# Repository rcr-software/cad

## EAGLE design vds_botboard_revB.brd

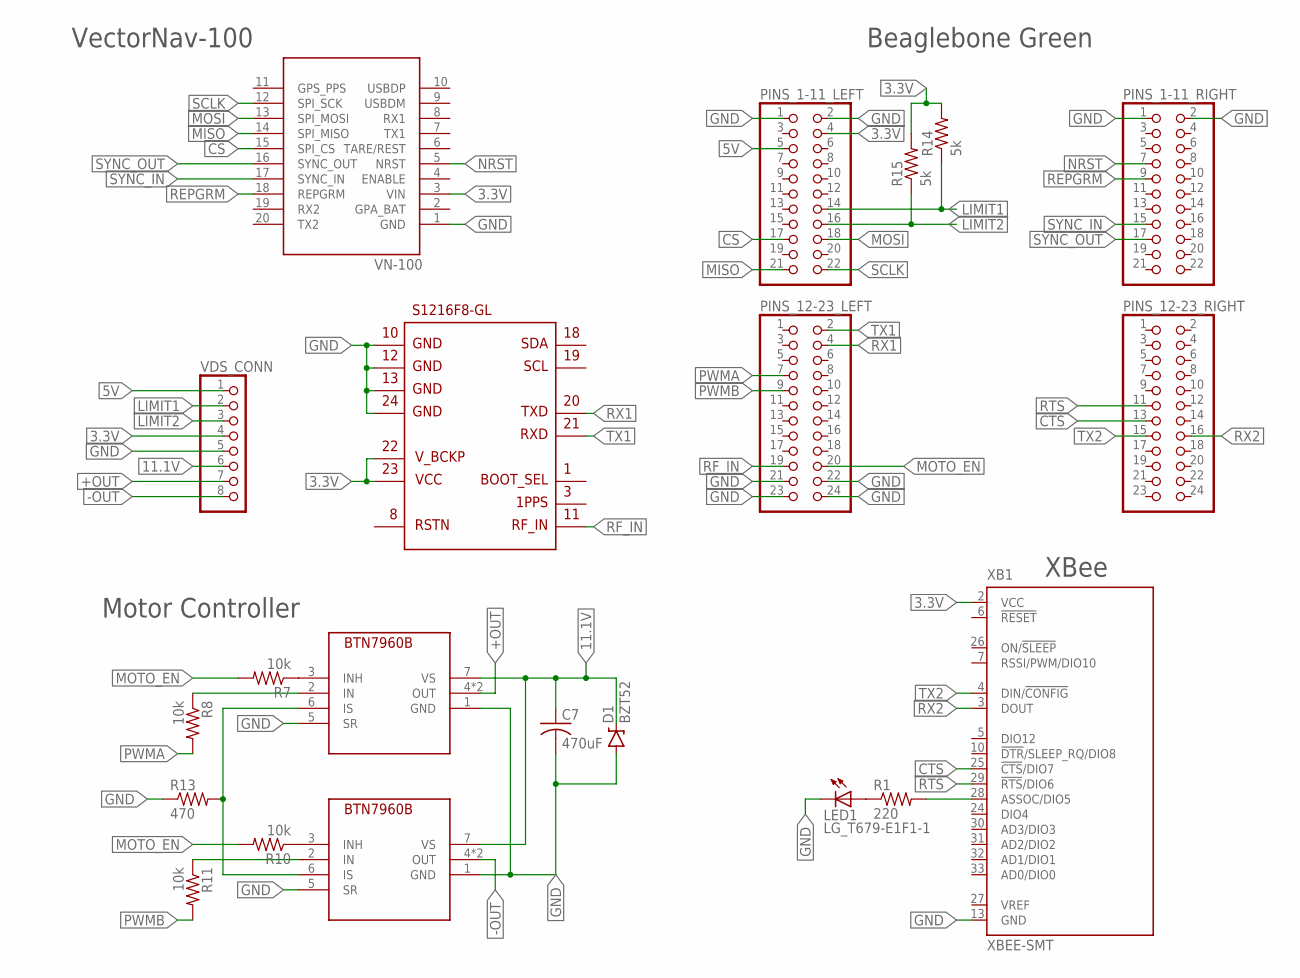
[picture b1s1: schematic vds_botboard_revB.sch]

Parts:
C7: 470uF; C050-024X044
D1: BZT52; DIODE-BZT52
JM1: S1216F8-GL
LED1: LG_T679-E1F1-1; PLCC2
PINS_1-11_LEFT, PINS_1-11_RIGHT: PINHD-2X11; 2X11
PINS_12-23_LEFT, PINS_12-23_RIGHT: PINHD-2X12; 2X12
R1: 220; 0204/5
R7, R8, R10, R11: 10k; 0204/5
R13: 470; 0204/5
R14, R15: 5k; 0204/5
U1, U2: INF-PG-TO263-7-1_L_1_BTN7960B; INF-PG-TO263-7-1_L_1PRIMARY
VDS_CONN: PINHD-1X8; 1X08
VN1: VECTORNAV-100; VN-100
XB1: XBEE-SMT

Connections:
3.3V: JM1.22, JM1.23, PINS_1-11_LEFT.4, R14.2, R15.2, VDS_CONN.4, VN1.3 (VIN), XB1.2 (VCC)
5V: PINS_1-11_LEFT.5, VDS_CONN.1
11.1V: C7.1, D1.C, U1.7 (VS), U2.7 (VS), VDS_CONN.6
+OUT: U1.4 (OUT), U1.8 (OUT), VDS_CONN.7
-OUT: U2.4 (OUT), U2.8 (OUT), VDS_CONN.8
COMM: R1.2, XB1.28 (ASSOC/DIO5)
CS: PINS_1-11_LEFT.17, VN1.15 (SPI_CS)
CTS: PINS_12-23_RIGHT.13, XB1.25 (!CTS!/DIO7)
GND: C7.2, D1.A, JM1.10, JM1.12, JM1.13, JM1.24, LED1.C, PINS_1-11_LEFT.1, PINS_1-11_LEFT.2, PINS_1-11_RIGHT.1, PINS_1-11_RIGHT.2, PINS_12-23_LEFT.21, PINS_12-23_LEFT.22, PINS_12-23_LEFT.23, PINS_12-23_LEFT.24, R13.1, U1.1 (GND), U1.5 (SR), U2.1 (GND), U2.5 (SR), VDS_CONN.5, VN1.1 (GND), XB1.13 (GND)
IS: R13.2, U1.6 (IS), U2.6 (IS)
LIMIT1: PINS_1-11_LEFT.14, R14.1, VDS_CONN.2
LIMIT2: PINS_1-11_LEFT.16, R15.1, VDS_CONN.3
MISO: PINS_1-11_LEFT.21, VN1.14 (SPI_MISO)
MOSI: PINS_1-11_LEFT.18, VN1.13 (SPI_MOSI)
MOTO_EN: PINS_12-23_LEFT.20, R7.2, R10.2
unnamed: LED1.A, R1.1
unnamed: R7.1, U1.3 (INH)
unnamed: R8.1, U1.2 (IN)
unnamed: R10.1, U2.3 (INH)
unnamed: R11.1, U2.2 (IN)
NRST: PINS_1-11_RIGHT.7, VN1.5 (NRST)
PWMA: PINS_12-23_LEFT.7, R8.2
PWMB: PINS_12-23_LEFT.9, R11.2
REPGRM: PINS_1-11_RIGHT.9, VN1.18 (REPGRM)
RF_IN: JM1.11, PINS_12-23_LEFT.19
RTS: PINS_12-23_RIGHT.11, XB1.29 (!RTS!/DIO6)
RX1: JM1.20, PINS_12-23_LEFT.4
RX2: PINS_12-23_RIGHT.16, XB1.3 (DOUT)
SCLK: PINS_1-11_LEFT.22, VN1.12 (SPI_SCK)
SYNC_IN: PINS_1-11_RIGHT.15, VN1.17 (SYNC_IN)
SYNC_OUT: PINS_1-11_RIGHT.17, VN1.16 (SYNC_OUT)
TX1: JM1.21, PINS_12-23_LEFT.2
TX2: PINS_12-23_RIGHT.15, XB1.4 (DIN/!CONFIG)

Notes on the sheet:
VectorNav-100
Motor Controller
Beaglebone Green
XBee

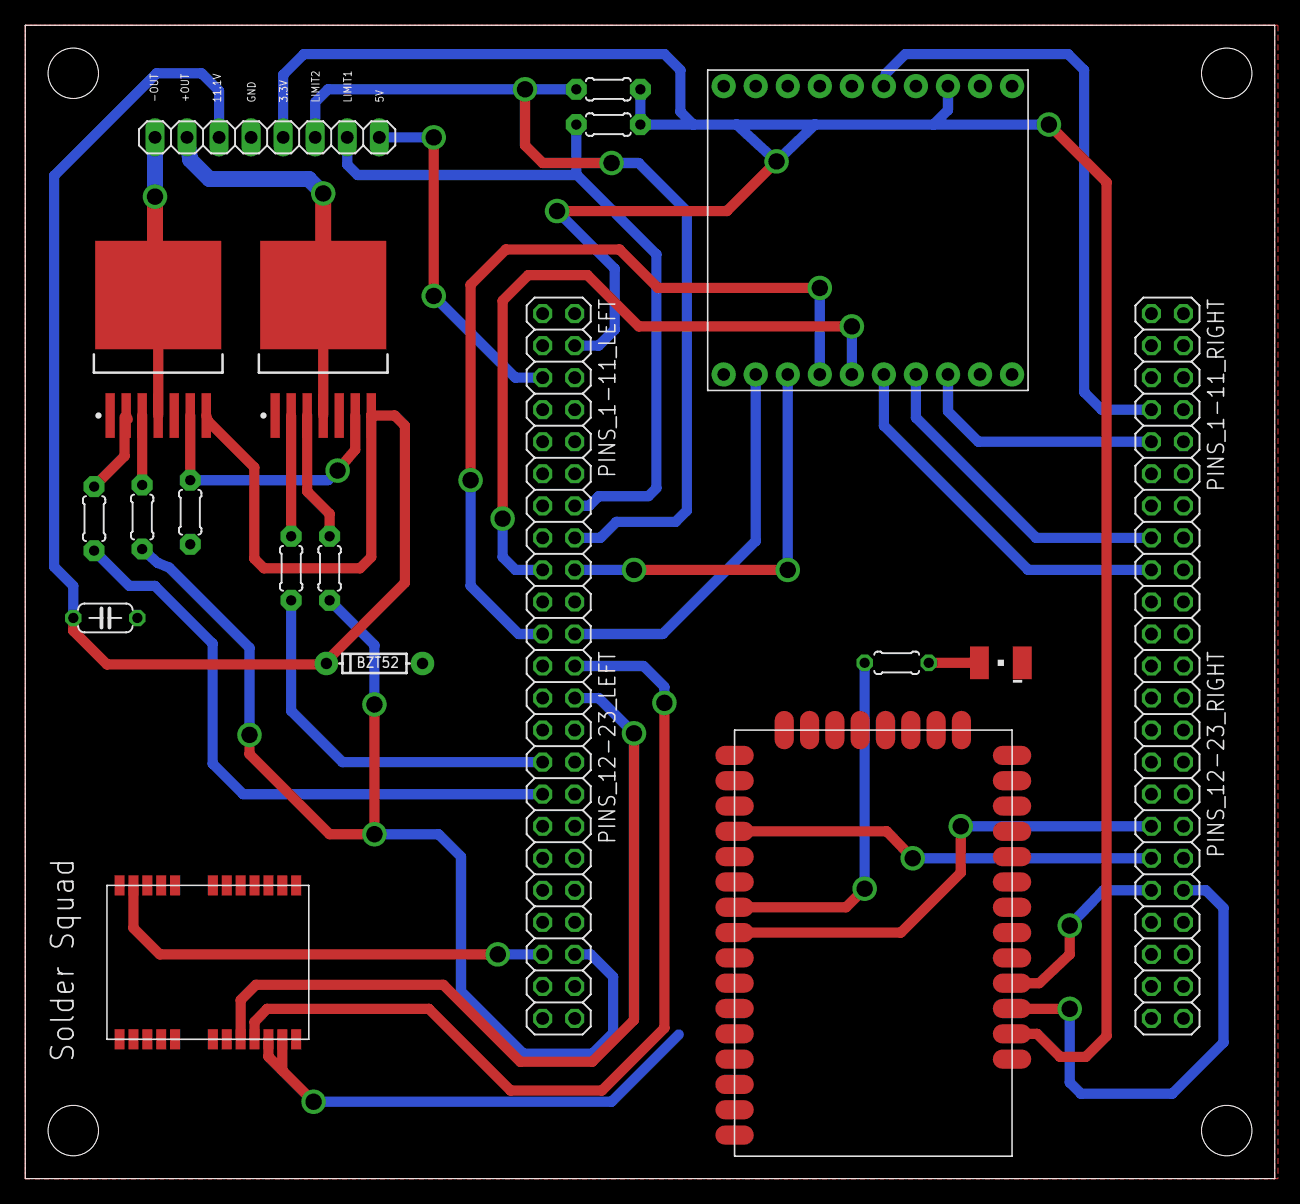
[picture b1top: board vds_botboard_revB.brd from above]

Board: 2 copper layers, 99.1 x 91.4 mm, 21 parts (0 on the bottom side), 33 nets.

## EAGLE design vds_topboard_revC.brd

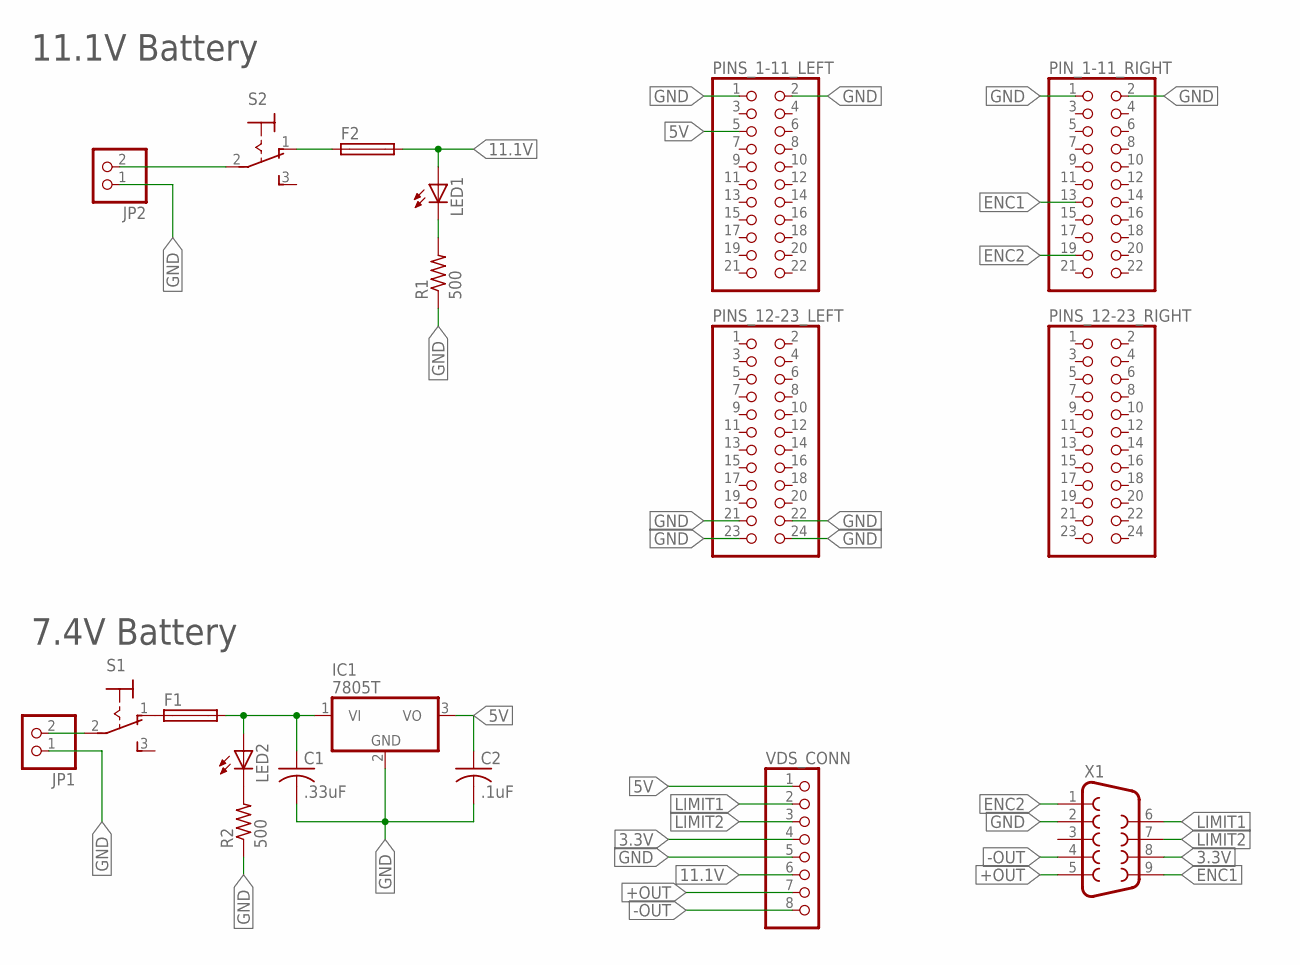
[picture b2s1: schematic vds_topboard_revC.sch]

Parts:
C1: .33uF; C025-030X050
C2: .1uF; C025-030X050
F1, F2: SH22,5
IC1: 7805T; TO220H
JP1, JP2: PINHD-1X2; 1X02
LED1, LED2: LED5MM
PINS_1-11_LEFT: PINHD-2X11; 2X11
PINS_12-23_LEFT, PINS_12-23_RIGHT: PINHD-2X12; 2X12
PIN_1-11_RIGHT: PINHD-2X11; 2X11
R1, R2: 500; 0204/5
S1, S2: 320-916
VDS_CONN: PINHD-1X8; 1X08
X1: F09VP

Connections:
3.3V: VDS_CONN.4, X1.8
5V: C2.1, IC1.3 (VO), PINS_1-11_LEFT.5, VDS_CONN.1
7.4VO: C1.1, F1.2, IC1.1 (VI), LED2.A
11.1V: F2.2, LED1.A, VDS_CONN.6
+OUT: VDS_CONN.7, X1.5
-OUT: VDS_CONN.8, X1.4
ENC1: PIN_1-11_RIGHT.13, X1.9
ENC2: PIN_1-11_RIGHT.19, X1.1
GND: C1.2, C2.2, IC1.2 (GND), JP1.1, JP2.1, PINS_1-11_LEFT.1, PINS_1-11_LEFT.2, PINS_12-23_LEFT.21, PINS_12-23_LEFT.22, PINS_12-23_LEFT.23, PINS_12-23_LEFT.24, PIN_1-11_RIGHT.1, PIN_1-11_RIGHT.2, R1.1, R2.1, VDS_CONN.5, X1.2
LIMIT1: VDS_CONN.2, X1.6
LIMIT2: VDS_CONN.3, X1.7
unnamed: JP1.2, S1.2
unnamed: JP2.2, S2.2
unnamed: F2.1, S2.1 (O)
unnamed: LED1.K (C), R1.2
unnamed: LED2.K (C), R2.2
unnamed: F1.1, S1.1 (O)

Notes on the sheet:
11.1V Battery
7.4V Battery

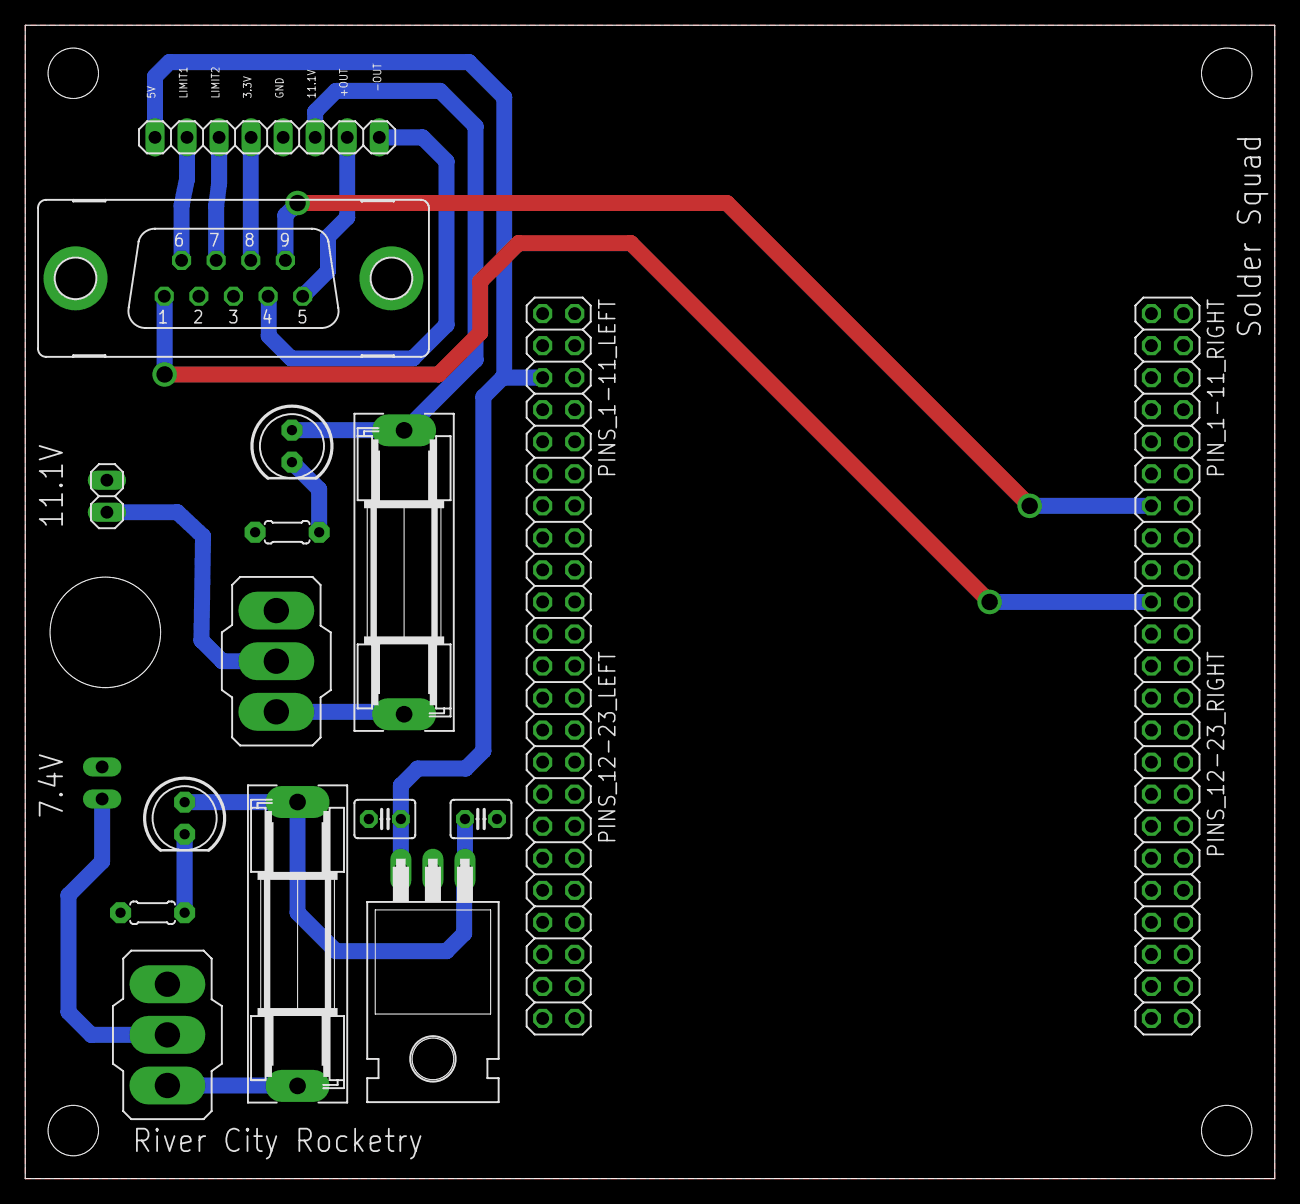
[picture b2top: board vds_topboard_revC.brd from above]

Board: 2 copper layers, 99.1 x 91.4 mm, 19 parts (1 on the bottom side), 17 nets.

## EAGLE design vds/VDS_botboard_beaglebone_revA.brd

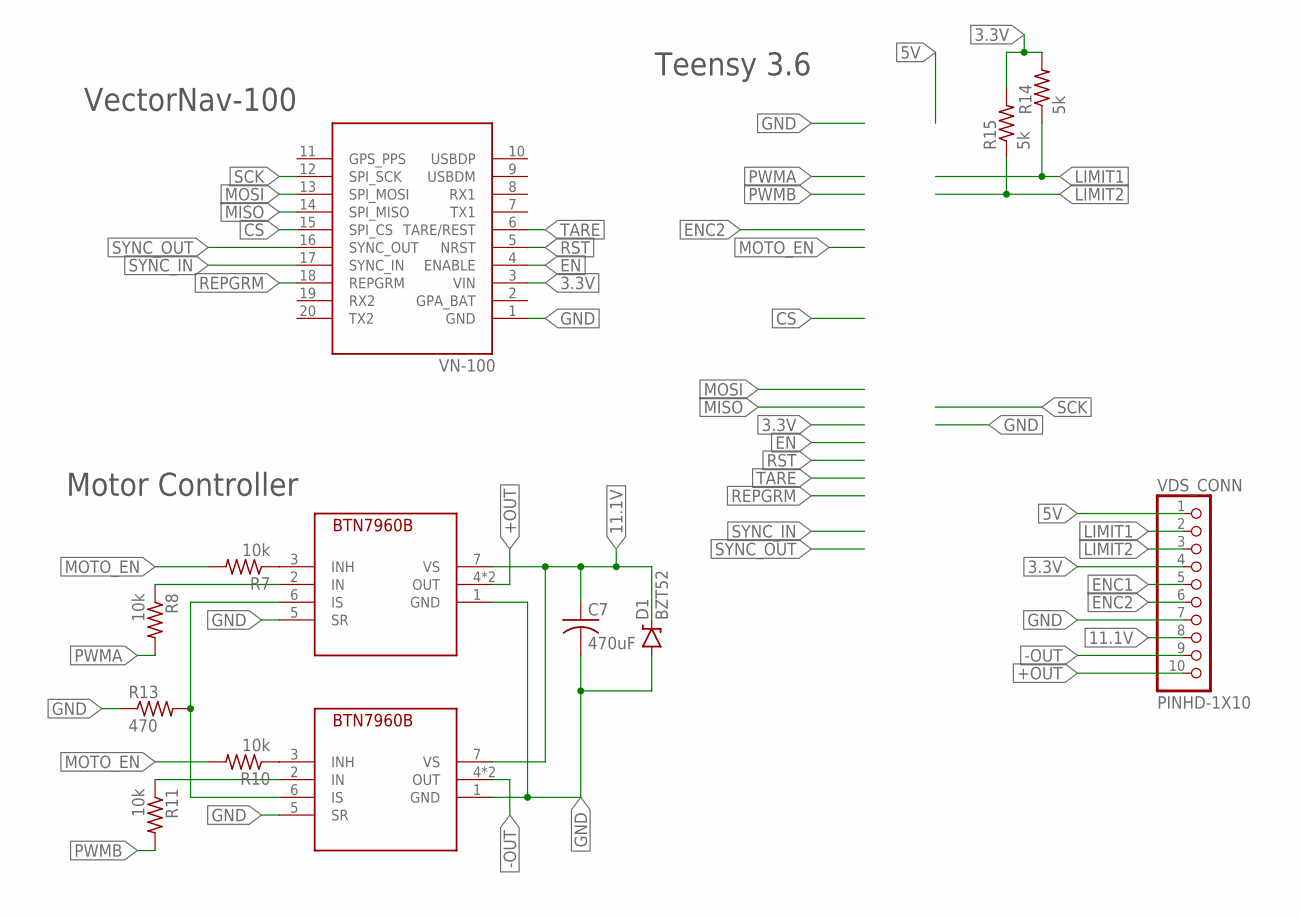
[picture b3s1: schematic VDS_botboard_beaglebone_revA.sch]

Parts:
C7: 470uF; C050-024X044
D1: BZT52; DIODE-BZT52
R7, R8, R10, R11: 10k; 0204/5
R13: 470; 0204/5
R14, R15: 5k; 0204/5
U1, U2: INF-PG-TO263-7-1_L_1_BTN7960B; INF-PG-TO263-7-1_L_1PRIMARY
VDS_CONN: PINHD-1X10; 1X10-BIG
VN1: VECTORNAV-100; VN-100

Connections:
3.3V: R14.2, R15.2, VDS_CONN.4, VN1.3 (VIN)
5V: VDS_CONN.1
11.1V: C7.1, D1.C, U1.7 (VS), U2.7 (VS), VDS_CONN.8
+OUT: U1.4 (OUT), U1.8 (OUT), VDS_CONN.10
-OUT: U2.4 (OUT), U2.8 (OUT), VDS_CONN.9
CS: VN1.15 (SPI_CS)
EN: VN1.4 (ENABLE)
ENC1: VDS_CONN.5
ENC2: VDS_CONN.6
GND: C7.2, D1.A, R13.1, U1.1 (GND), U1.5 (SR), U2.1 (GND), U2.5 (SR), VDS_CONN.7, VN1.1 (GND)
IS: R13.2, U1.6 (IS), U2.6 (IS)
LIMIT1: R14.1, VDS_CONN.2
LIMIT2: R15.1, VDS_CONN.3
MISO: VN1.14 (SPI_MISO)
MOSI: VN1.13 (SPI_MOSI)
MOTO_EN: R7.2, R10.2
unnamed: R7.1, U1.3 (INH)
unnamed: R8.1, U1.2 (IN)
unnamed: R10.1, U2.3 (INH)
unnamed: R11.1, U2.2 (IN)
PWMA: R8.2
PWMB: R11.2
REPGRM: VN1.18 (REPGRM)
RST: VN1.5 (NRST)
SCK: VN1.12 (SPI_SCK)
SYNC_IN: VN1.17 (SYNC_IN)
SYNC_OUT: VN1.16 (SYNC_OUT)
TARE: VN1.6 (TARE/REST)

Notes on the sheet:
VectorNav-100
Motor Controller
Teensy 3.6

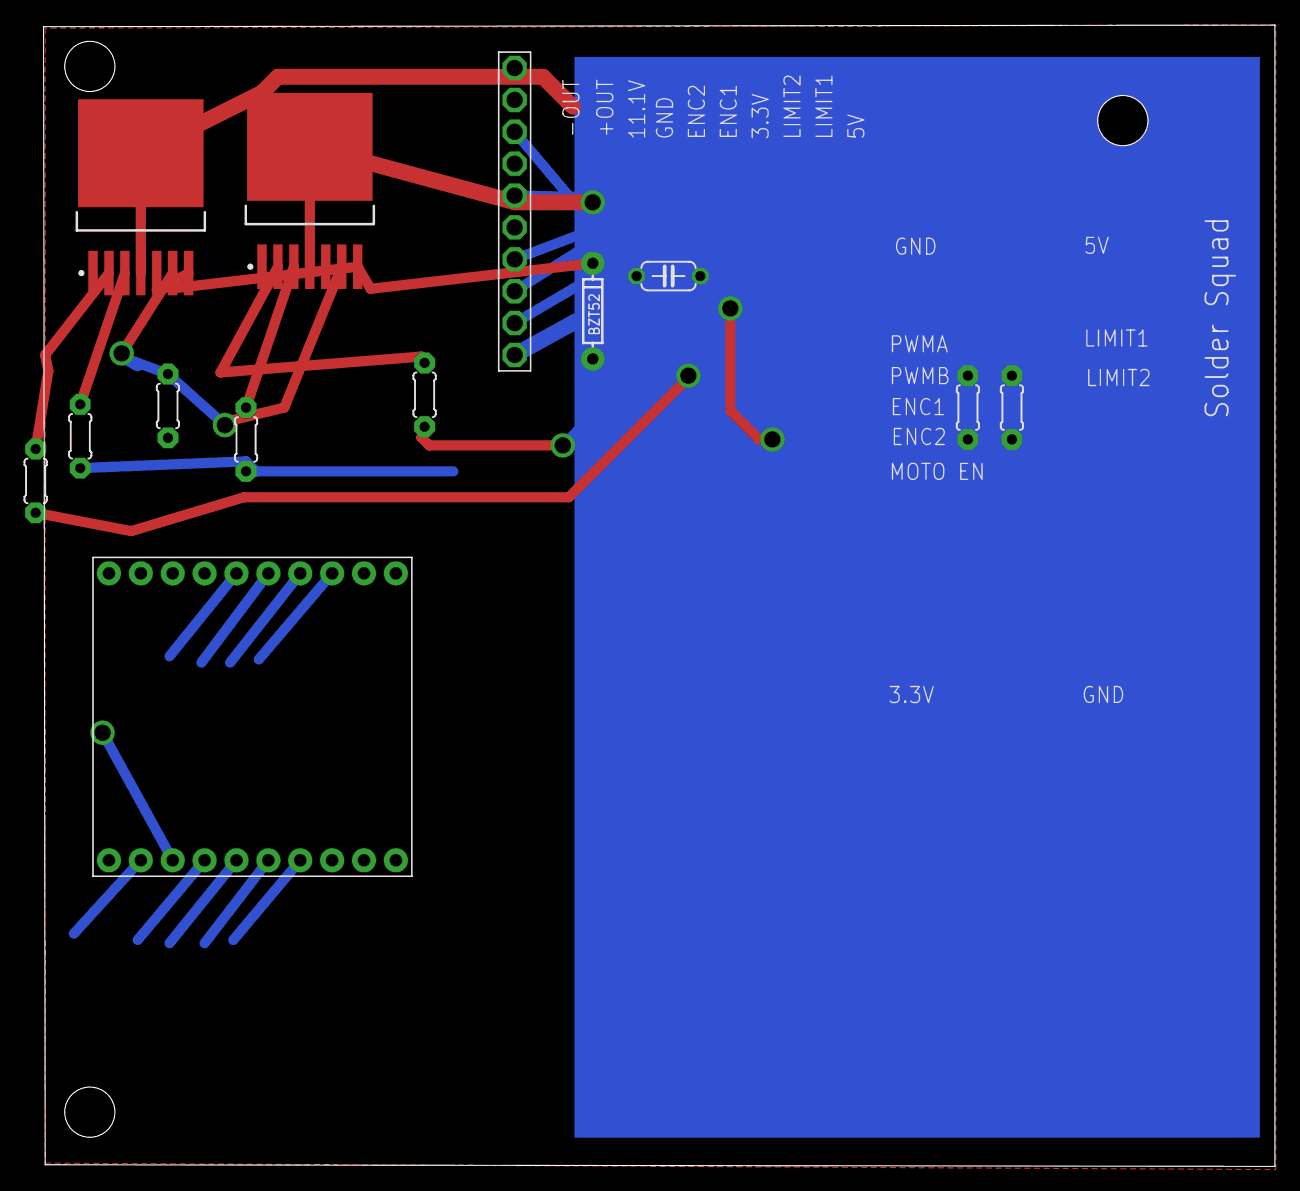
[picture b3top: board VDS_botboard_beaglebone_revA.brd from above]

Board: 2 copper layers, 98.1 x 90.9 mm, 13 parts (0 on the bottom side), 13 nets.

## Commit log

2018-01-02 add vds folder
2018-01-02 Add files via upload
    Alora's beaglebone PCB
2018-01-05 vds pcb board w/ beaglebone
2018-01-05 Manufactured PCB files
    1/5/2018 - first boards sent for manufacturing
2018-01-05 fixed bottom board
2018-01-06 fixed bottom board 3.3V
2018-01-08 Updated 1-8-18, fixed drill size

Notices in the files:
parts and their libraries:
SparkFun-DiscreteSemi: Licensing: Creative Commons ShareAlike 4.0 International - https://creativecommons.org/licenses/by-sa/4.0
